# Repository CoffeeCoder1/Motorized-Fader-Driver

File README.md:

# Motorized Fader Driver

A self-contained PCB for controlling motorized faders, based on the RP2040 microcontroller and DRV8833 motor driver. This project allows for motorized faders to be controlled over I2C, allowing for easier control over banks of faders.

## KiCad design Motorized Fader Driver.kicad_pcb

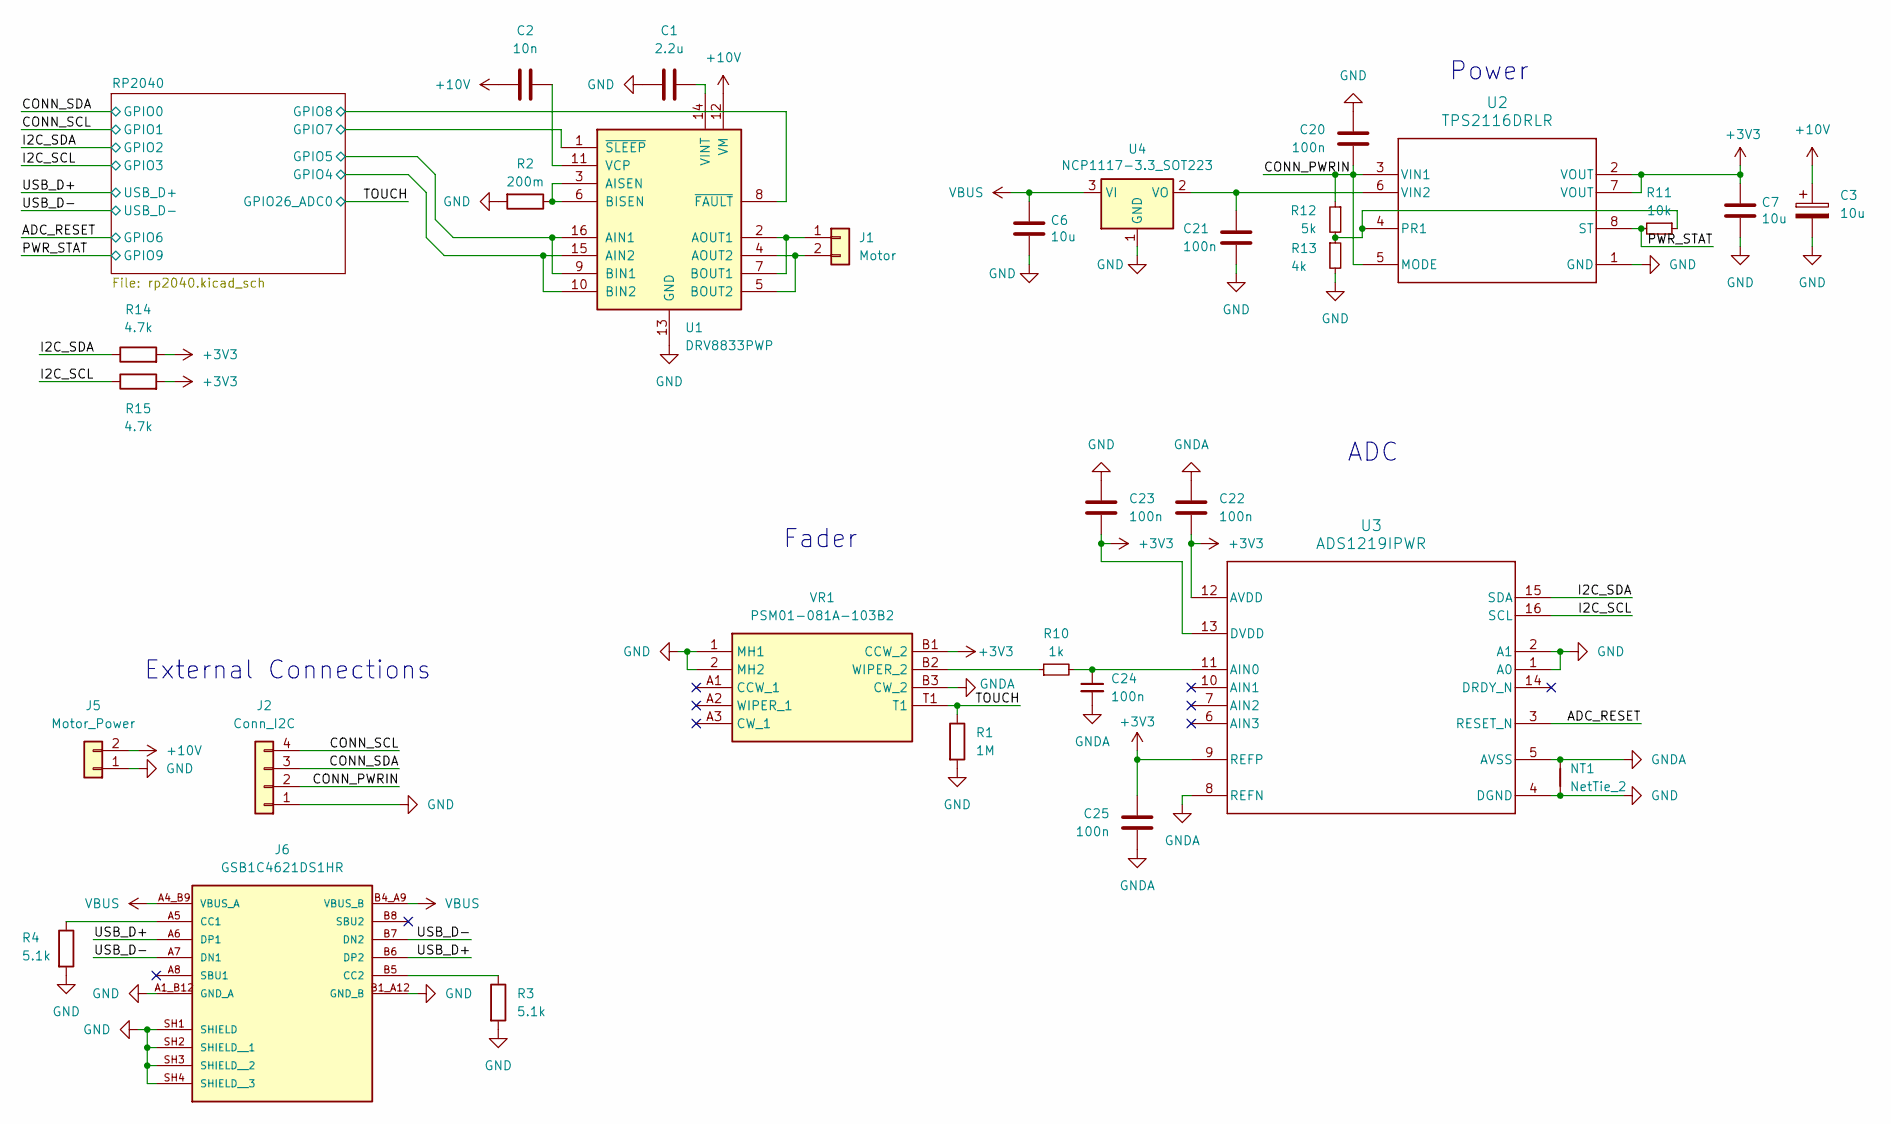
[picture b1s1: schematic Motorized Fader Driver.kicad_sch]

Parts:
C1: 2.2u; C_0603_1608Metric; LCSC Part C76612
C2: 10n; C_0603_1608Metric; LCSC Part C445735
C3: 10u; C_0603_1608Metric; LCSC Part C178496
C6, C7: 10u; C_0603_1608Metric; LCSC Part C76609
C20, C21, C22, C23, C24, C25: 100n; C_0603_1608Metric; LCSC Part C76711
J1: Motor; PinHeader_1x02_P2.54mm_Vertical
J2: Conn_I2C; CONN_SM04B-SRSS-TB_JST; LCSC Part C160404
J5: Motor_Power; JST_EH_S2B-EH_1x02_P2.50mm_Horizontal; LCSC Part C514173
J6: GSB1C4621DS1HR; AMPHENOL_GSB1C4621DS1HR; PARTREV AX1; LCSC Part C20657289
NT1: NetTie_2; NetTie-2_SMD_Pad0.5mm
R1: 1M; R_0603_1608Metric; LCSC Part C2907003
R2: 200m; R_0603_1608Metric; LCSC Part C79773
R3, R4: 5.1k; R_0603_1608Metric; LCSC Part C2907044
R10: 1k; R_0603_1608Metric; LCSC Part C21190
R11: 10k; R_0603_1608Metric; LCSC Part C98220
R12: 5k; R_0603_1608Metric; LCSC Part C166926
R13: 4k; R_0603_1608Metric; LCSC Part C2984443
R14, R15: 4.7k; R_0603_1608Metric; LCSC Part C99782
U1: DRV8833PWP; HTSSOP-16-1EP_4.4x5mm_P0.65mm_EP3.4x5mm_Mask2.46x2.31mm_The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; LCSC Part C1556089
U2: TPS2116DRLR; DRL0008A-MFG; LCSC Part C3235557
U3: ADS1219IPWR; PW0016A_L; LCSC Part C2869313
U4: NCP1117-3.3_SOT223; SOT-223-3_TabPin2; LCSC Part C146799
VR1: PSM01-081A-103B2; PSM01081A103B2; Manufacturer_Part_Number PSM01-081A-103B2; Mouser Part Number 652-PSM01081A103B2

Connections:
+3V3: C7.1, C22.2, C23.1, C25.1, R14.2, R15.2, U2.2 (VOUT), U2.7 (VOUT), U3.9 (REFP), U3.12 (AVDD), U3.13 (DVDD), VR1.B1 (CCW_2); also elsewhere on the board
+10V: C2.1, C3.1, J5.2, U1.12 (VM)
/ADC_RESET: U3.3 (RESET_N); also elsewhere on the board
/CONN_PWRIN: C20.1, J2.2, R12.1, U2.3 (VIN1), U2.5 (MODE)
/CONN_SCL: J2.4; also elsewhere on the board
/CONN_SDA: J2.3; also elsewhere on the board
/I2C_SCL: R15.1, U3.16 (SCL); also elsewhere on the board
/I2C_SDA: R14.1, U3.15 (SDA); also elsewhere on the board
/PWR_STAT: R11.2, U2.8 (ST); also elsewhere on the board
/RP2040/GPIO4: U1.10 (BIN2), U1.15 (AIN2); also elsewhere on the board
/RP2040/GPIO5: U1.9 (BIN1), U1.16 (AIN1); also elsewhere on the board
/RP2040/GPIO7: U1.1 (~SLEEP); also elsewhere on the board
/RP2040/GPIO8: U1.8 (~FAULT); also elsewhere on the board
/TOUCH: R1.1, VR1.T1; also elsewhere on the board
/USB_D+: J6.A6 (DP1), J6.B6 (DP2); also elsewhere on the board
/USB_D-: J6.A7 (DN1), J6.B7 (DN2); also elsewhere on the board
GND: C1.1, C3.2, C6.2, C7.2, C20.2, C21.2, C23.2, J2.1, J5.1, J6.A1_B12 (GND_A), J6.B1_A12 (GND_B), J6.SH1 (SHIELD), J6.SH2 (SHIELD__1), J6.SH3 (SHIELD__2), J6.SH4 (SHIELD__3), NT1.1, R1.2, R2.2, R3.2, R4.2, R13.2, U1.13 (GND), U1.17 (GND), U2.1 (GND), U3.1 (A0), U3.2 (A1), U3.4 (DGND), U4.1 (GND), VR1.1 (MH1), VR1.2 (MH2); also elsewhere on the board
GNDA: C22.1, C24.2, C25.2, NT1.2, U3.5 (AVSS), U3.8 (REFN), VR1.B3 (CW_2)
unnamed: J1.1, U1.2 (AOUT1), U1.7 (BOUT1)
unnamed: J1.2, U1.4 (AOUT2), U1.5 (BOUT2)
unnamed: J6.A5 (CC1), R4.1
unnamed: J6.B5 (CC2), R3.1
unnamed: R2.1, U1.3 (AISEN), U1.6 (BISEN)
unnamed: C2.2, U1.11 (VCP)
unnamed: C1.2, U1.14 (VINT)
unnamed: R11.1, R12.2, R13.1, U2.4 (PR1)
unnamed: C21.1, U2.6 (VIN2), U4.2 (VO)
unnamed: C24.1, R10.2, U3.11 (AIN0)
unnamed: R10.1, VR1.B2 (WIPER_2)
VBUS: C6.1, J6.A4_B9 (VBUS_A), J6.B4_A9 (VBUS_B), U4.3 (VI)

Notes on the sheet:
External Connections
ADC
Power
Fader

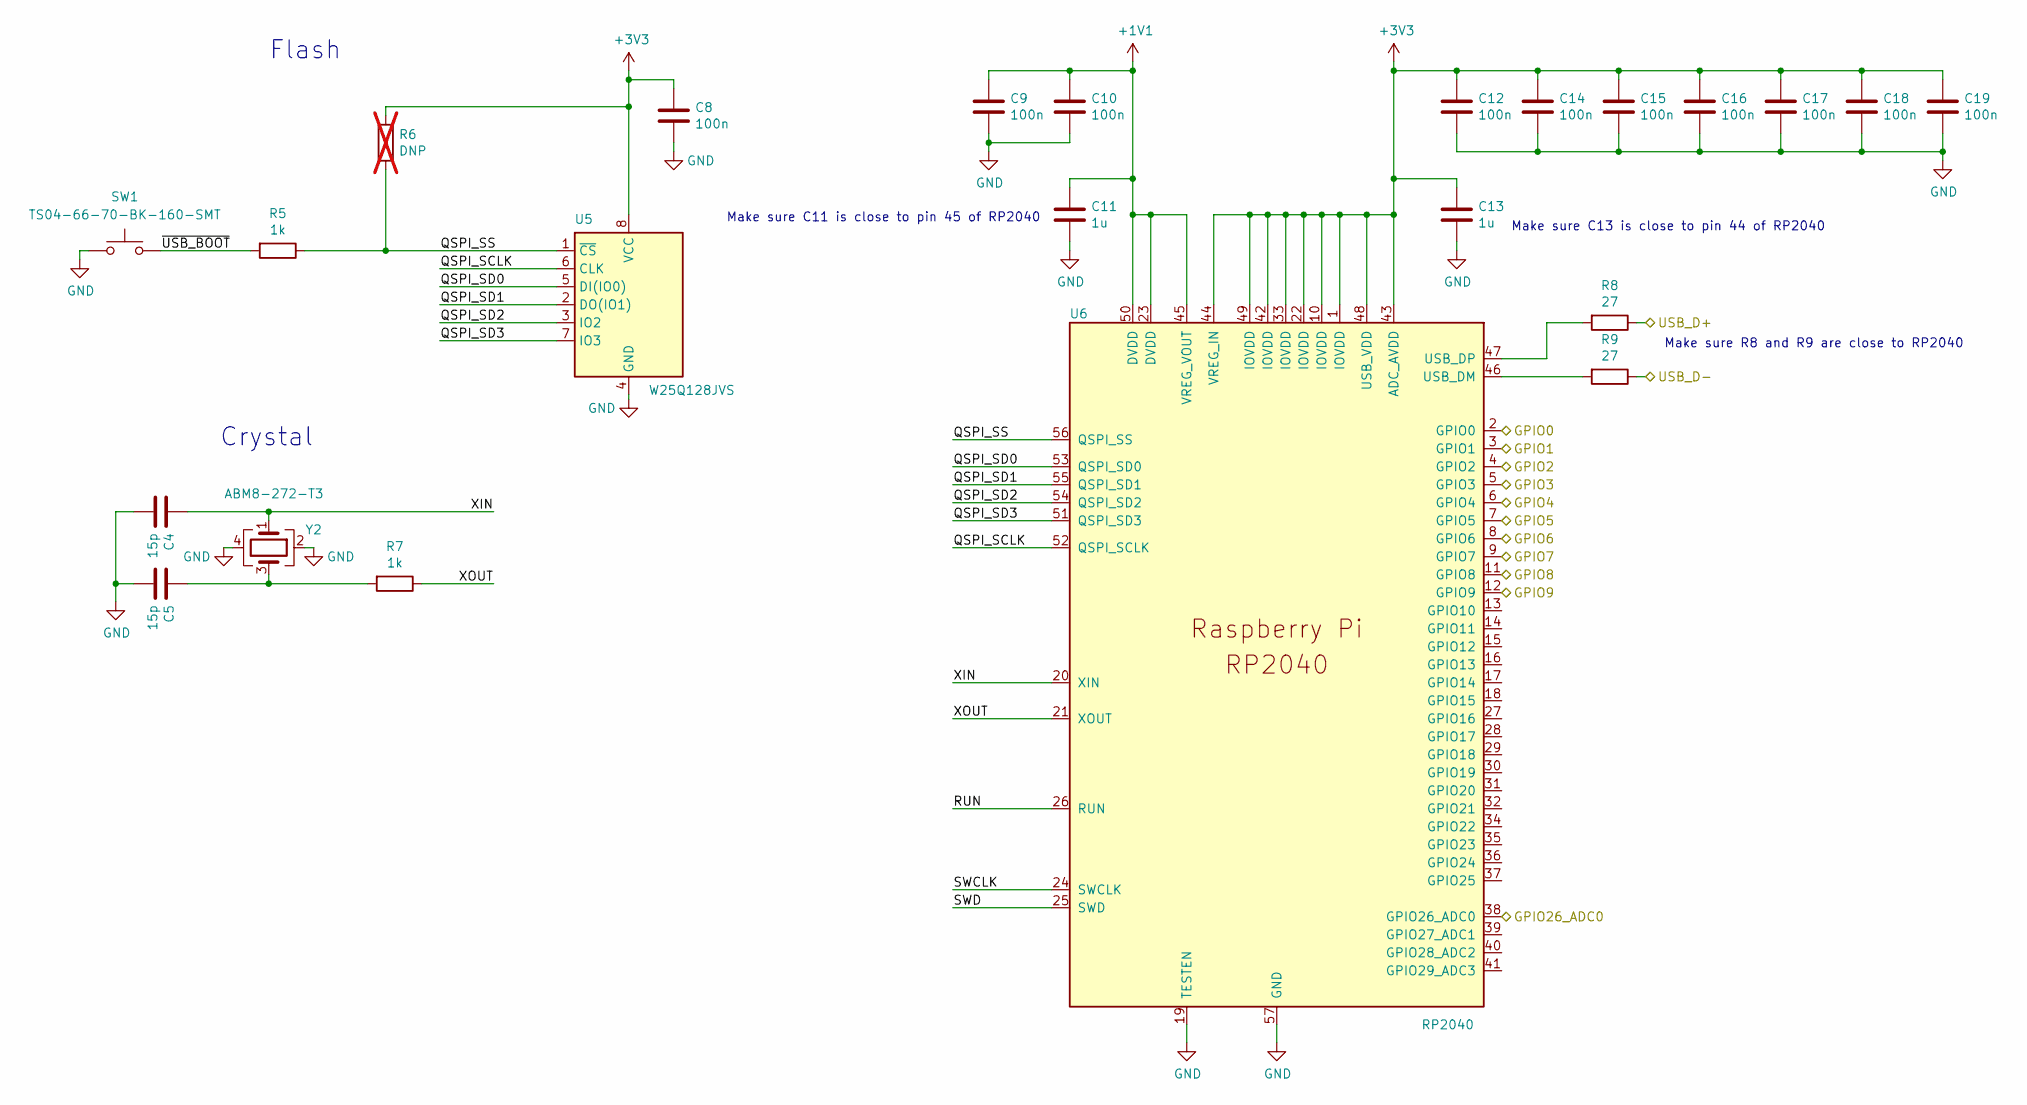
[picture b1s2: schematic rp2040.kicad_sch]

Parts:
C4, C5: 15p; C_0603_1608Metric; LCSC Part C342889
C8, C9, C10, C12, C14, C15, C16, C17, C18, C19: 100n; C_0603_1608Metric; LCSC Part C76711
C11, C13: 1u; C_0603_1608Metric; LCSC Part C76706
R5, R7: 1k; R_0603_1608Metric; LCSC Part C21190
R6: DNP; R_0603_1608Metric; not fitted
R8, R9: 27; R_0603_1608Metric; LCSC Part C2907021
SW1: TS04-66-70-BK-160-SMT; SW_TS04-66-70-BK-160-SMT; LCSC Part C4364350
U5: W25Q128JVS; SOIC-8_5.23x5.23mm_P1.27mm; LCSC Part C97521
U6: RP2040; QFN-56-1EP_7x7mm_P0.4mm_EP3.2x3.2mm_ThermalVias; LCSC Part C2040
Y2: ABM8-272-T3; Crystal_SMD_3225-4Pin_3.2x2.5mm; LCSC Part C20625731

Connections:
+1V1: C9.1, C10.1, C11.1, U6.23 (DVDD), U6.45 (VREG_VOUT), U6.50 (DVDD)
+3V3: C8.1, C12.1, C13.1, C14.1, C15.1, C16.1, C17.1, C18.1, C19.1, R6.1, U5.8 (VCC), U6.1 (IOVDD), U6.10 (IOVDD), U6.22 (IOVDD), U6.33 (IOVDD), U6.42 (IOVDD), U6.43 (ADC_AVDD), U6.44 (VREG_IN), U6.48 (USB_VDD), U6.49 (IOVDD); also elsewhere on the board
/ADC_RESET: U6.8 (GPIO6); also elsewhere on the board
/CONN_SCL: U6.3 (GPIO1); also elsewhere on the board
/CONN_SDA: U6.2 (GPIO0); also elsewhere on the board
/I2C_SCL: U6.5 (GPIO3); also elsewhere on the board
/I2C_SDA: U6.4 (GPIO2); also elsewhere on the board
/PWR_STAT: U6.12 (GPIO9); also elsewhere on the board
/RP2040/GPIO4: U6.6 (GPIO4); also elsewhere on the board
/RP2040/GPIO5: U6.7 (GPIO5); also elsewhere on the board
/RP2040/GPIO7: U6.9 (GPIO7); also elsewhere on the board
/RP2040/GPIO8: U6.11 (GPIO8); also elsewhere on the board
/RP2040/QSPI_SCLK: U5.6 (CLK), U6.52 (QSPI_SCLK)
/RP2040/QSPI_SD0: U5.5 (DI(IO0)), U6.53 (QSPI_SD0)
/RP2040/QSPI_SD1: U5.2 (DO(IO1)), U6.55 (QSPI_SD1)
/RP2040/QSPI_SD2: U5.3 (IO2), U6.54 (QSPI_SD2)
/RP2040/QSPI_SD3: U5.7 (IO3), U6.51 (QSPI_SD3)
/RP2040/QSPI_SS: R5.1, R6.2, U5.1 (~CS), U6.56 (QSPI_SS)
/RP2040/RUN: U6.26 (RUN)
/RP2040/SWCLK: U6.24 (SWCLK)
/RP2040/SWD: U6.25 (SWD)
/RP2040/XIN: C4.1, U6.20 (XIN), Y2.1
/RP2040/XOUT: R7.1, U6.21 (XOUT)
/RP2040/~USB_BOOT: R5.2, SW1.2
/TOUCH: U6.38 (GPIO26_ADC0); also elsewhere on the board
/USB_D+: R8.1; also elsewhere on the board
/USB_D-: R9.1; also elsewhere on the board
GND: C4.2, C5.2, C8.2, C9.2, C10.2, C11.2, C12.2, C13.2, C14.2, C15.2, C16.2, C17.2, C18.2, C19.2, SW1.1, U5.4 (GND), U6.19 (TESTEN), U6.57 (GND), Y2.2, Y2.4; also elsewhere on the board
unnamed: C5.1, R7.2, Y2.3
unnamed: R9.2, U6.46 (USB_DM)
unnamed: R8.2, U6.47 (USB_DP)

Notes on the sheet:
Flash
Make sure R8 and R9 are close to RP2040
Make sure C11 is close to pin 45 of RP2040
Make sure C13 is close to pin 44 of RP2040
Crystal

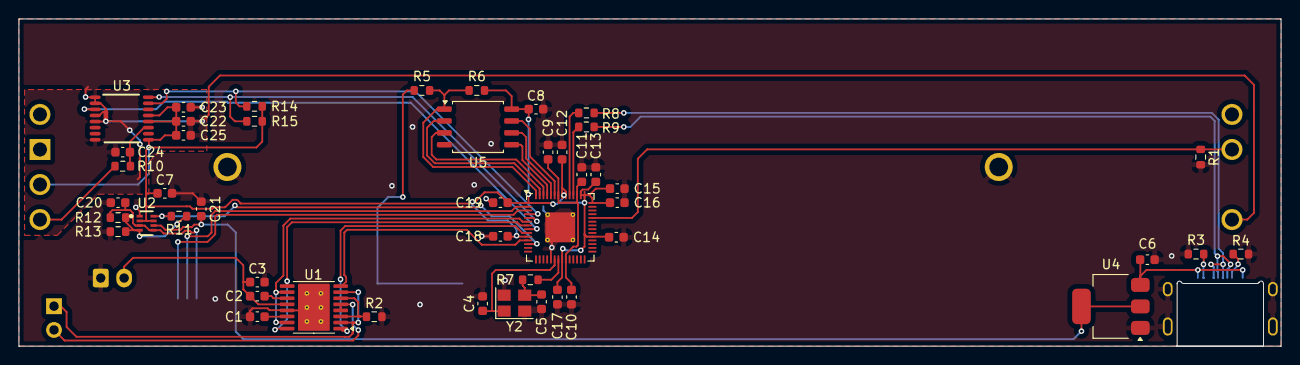
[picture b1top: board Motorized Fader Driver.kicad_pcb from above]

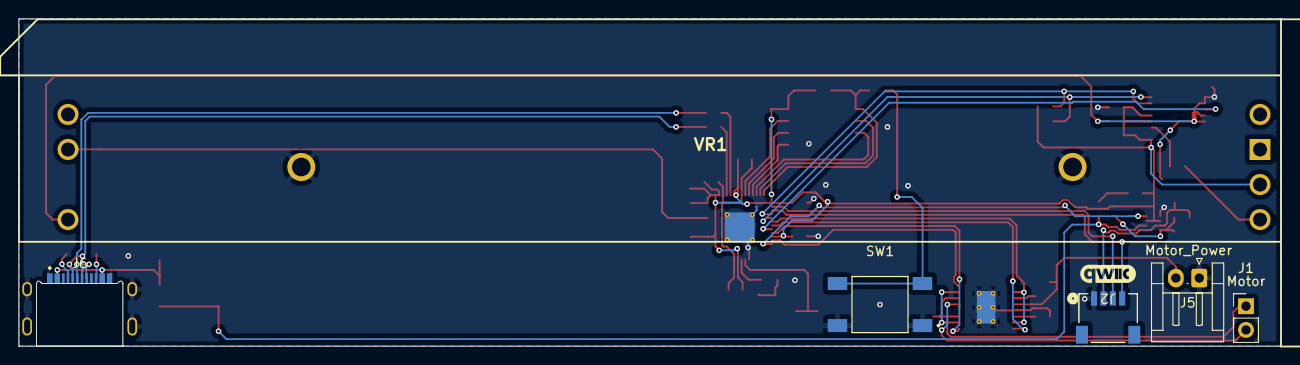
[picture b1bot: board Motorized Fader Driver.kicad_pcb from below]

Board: 2 copper layers, 135.0 x 35.0 mm, 54 parts (6 on the bottom side), 43 nets.

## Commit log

2025-01-31 Initial version
2025-01-31 Add a README
2025-01-31 Update PCB
2025-05-01 Add .DS_Store to the gitignore
2025-05-01 Finish most of the schematic design
    The majority of the schematic is in a pretty finalized state now. Also
    some more work on the PCB has been done.
2025-05-02 Finish routing most of the PCB
    The PCB should work now for the most part. Also fixes some miscellaneous
    schematic things and swaps out a few components.
2025-05-08 Route more things and add LCSC part numbers for things
    The LCSC part numbers allow for JLCPCB's PCBA tool to find the parts.
2025-10-21 Add a debug connector to the schematic
    Adds a Paw-Connect debug connector. Not sure if its actually hooked up
    yet, since its been a while since I've touched this project and I don't
    have KiCad on this computer, but it at least exists in the schematic.
